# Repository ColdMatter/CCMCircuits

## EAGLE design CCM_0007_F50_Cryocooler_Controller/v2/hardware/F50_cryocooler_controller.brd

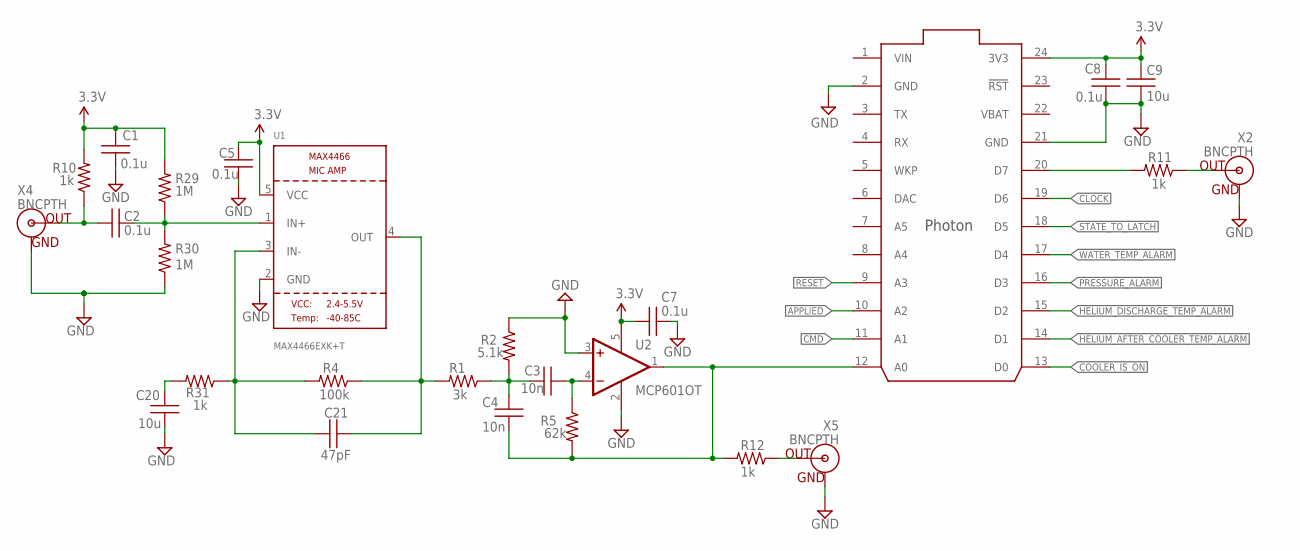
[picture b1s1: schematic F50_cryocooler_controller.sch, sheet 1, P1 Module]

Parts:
C1, C2, C5, C7, C8: 0.1u; 0603
C3, C4: 10n; 0603
C9: 10u; 0805
C20: 10u; 0603
C21: 47pF; 0603
R1: 3k; 0603
R2: 5.1k; 0603
R4: 100k; 0603
R5: 62k; 0603
R10, R11, R12, R31: 1k; 0603
R29, R30: 1M; 0603
U1: MAX4466EXK+T; SC70-5
U2: MCP601OT; SOT23-5
U3: PHOTON_WITH_HEADERS; PHOTON
X2, X4, X5: BNCPTH; BNC

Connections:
3.3V: C1.1, C5.1, C7.1, C8.1, C9.2, R10.2, R29.2, U1.5 (VCC), U2.5 (V+), U3.24 (3V3)
APPLIED: U3.10 (A2); also elsewhere on the board
AUDIO_IN: C21.2, R1.2, R4.1, U1.4 (OUT)
CLOCK: U3.19 (D6); also elsewhere on the board
CMD: U3.11 (A1); also elsewhere on the board
COOLER_IS_ON: U3.13 (D0); also elsewhere on the board
GND: C1.2, C5.2, C7.2, C8.2, C9.1, C20.2, R2.1, R30.1, U1.2 (GND), U2.2 (V-), U2.3 (+IN), U3.2 (GND), U3.21 (GND), X2.GND, X4.GND, X5.GND; also elsewhere on the board
HELIUM_AFTER_COOLER_TEMP_ALARM: U3.14 (D1); also elsewhere on the board
HELIUM_DISCHARGE_TEMP_ALARM: U3.15 (D2); also elsewhere on the board
unnamed: C2.1, R10.1, X4.S (OUT)
unnamed: C2.2, R29.1, R30.2, U1.1 (IN+)
unnamed: C21.1, R4.2, R31.1, U1.3 (IN-)
unnamed: C20.1, R31.2
unnamed: C3.1, C4.2, R1.1, R2.2
unnamed: C3.2, R5.1, U2.4 (-IN)
unnamed: R11.2, U3.20 (D7)
unnamed: C4.1, R5.2, R12.2, U2.1 (OUT), U3.12 (A0)
PRESSURE_ALARM: U3.16 (D3); also elsewhere on the board
RESET: U3.9 (A3); also elsewhere on the board
STATE_TO_LATCH: U3.18 (D5); also elsewhere on the board
SYNC_OUT: R11.1, X2.S (OUT)
TRIGGER_OUT: R12.1, X5.S (OUT)
VBAT: U3.22 (VBAT)
VIN: U3.1 (VIN)
WATER_TEMP_ALARM: U3.17 (D4); also elsewhere on the board

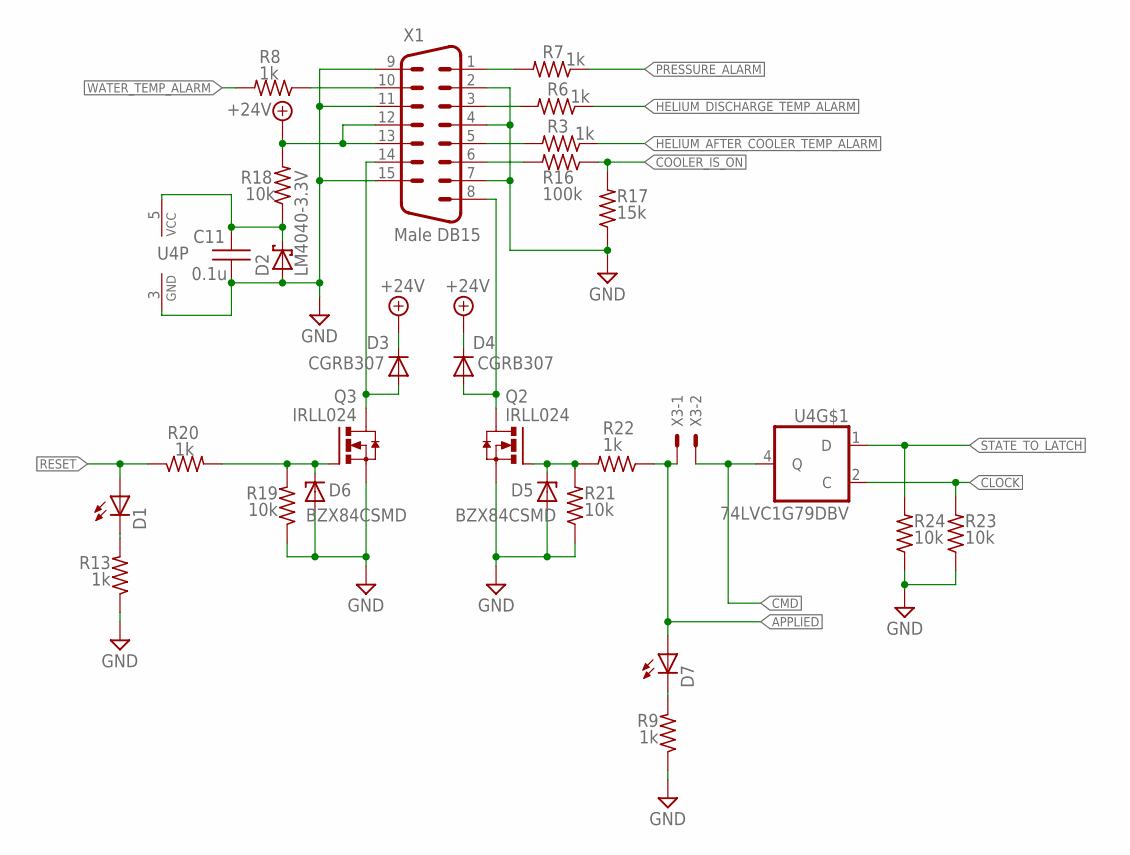
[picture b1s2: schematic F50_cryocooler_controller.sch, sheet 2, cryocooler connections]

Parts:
C11: 0.1u; 0603
D1, D7: LED0603
D2: LM4040-3.3V; SOT23
D3, D4: CGRB307; DO214AA
D5, D6: BZX84CSMD; TO236
Q2, Q3: IRLL024; SOT223
R3, R6, R7, R8, R9, R13, R20, R22: 1k; 0603
R16: 100k; 0603
R17: 15k; 0603
R18, R19, R21, R23, R24: 10k; 0603
U4: 74LVC1G79DBV; SOT23-5
X1: Male DB15; M15HP
X3: 22-23-2021

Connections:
+24V: D3.C, D4.C, R18.2, X1.12, X1.13
APPLIED: D7.A, R22.1, X3.1; also elsewhere on the board
CLOCK: R23.2, U4.2 (C); also elsewhere on the board
CMD: U4.4 (Q), X3.2; also elsewhere on the board
COOLER_IS_ON: R16.1, R17.2; also elsewhere on the board
GND: C11.2, D2.2 (A), D5.A, D6.A, Q2.3 (S), Q3.3 (S), R9.1, R13.1, R17.1, R19.1, R21.1, R23.1, R24.1, U4.3 (GND), X1.2, X1.4, X1.7, X1.9, X1.11, X1.15; also elsewhere on the board
HELIUM_AFTER_COOLER_TEMP_ALARM: R3.1; also elsewhere on the board
HELIUM_DISCHARGE_TEMP_ALARM: R6.1; also elsewhere on the board
unnamed: R8.1, X1.10
unnamed: R16.2, X1.6
unnamed: R7.2, X1.1
unnamed: D4.A, Q2.4 (D), X1.8
unnamed: R6.2, X1.3
unnamed: D5.C, Q2.1 (G), R21.2, R22.2
unnamed: C11.1, D2.1 (C), R18.1, U4.5 (VCC)
unnamed: R3.2, X1.5
unnamed: D1.C, R13.2
unnamed: D7.C, R9.2
unnamed: D3.A, Q3.4 (D), X1.14
unnamed: D6.C, Q3.1 (G), R19.2, R20.2
PRESSURE_ALARM: R7.1; also elsewhere on the board
RESET: D1.A, R20.1; also elsewhere on the board
STATE_TO_LATCH: R24.2, U4.1 (D); also elsewhere on the board
WATER_TEMP_ALARM: R8.2; also elsewhere on the board

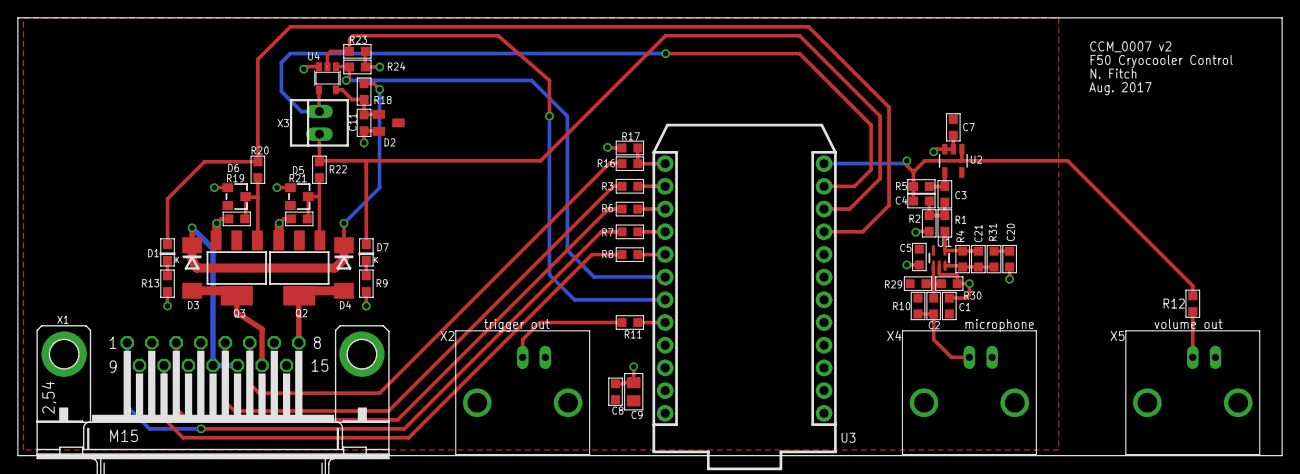
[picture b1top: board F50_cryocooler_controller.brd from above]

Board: 2 copper layers, 141.5 x 49.0 mm, 54 parts (0 on the bottom side), 36 nets.

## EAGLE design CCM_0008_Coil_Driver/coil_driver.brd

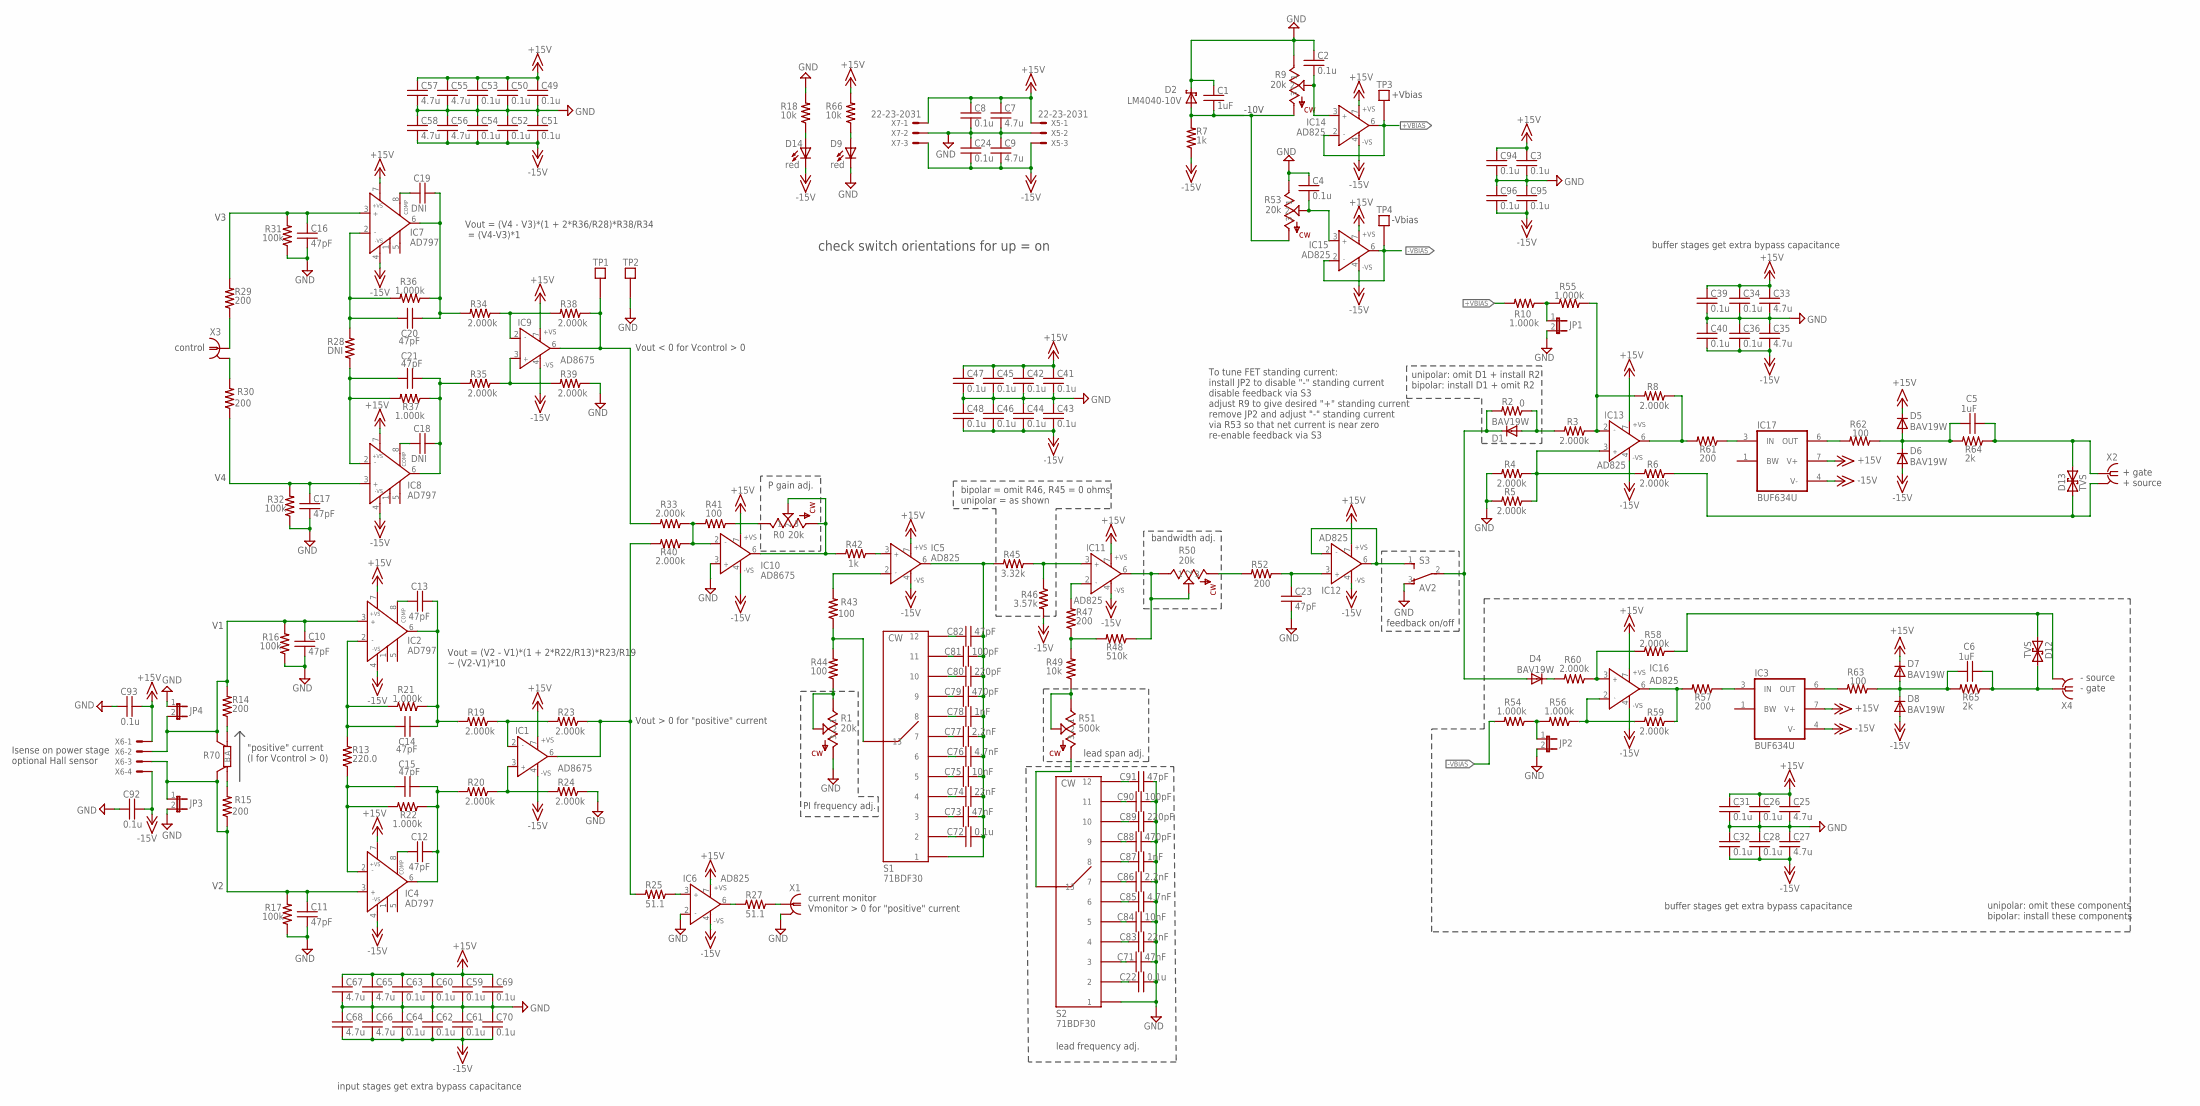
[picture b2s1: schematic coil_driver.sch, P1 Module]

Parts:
C1, C5, C6: 1uF; 0603
C2, C3, C4, C8, C22, C24, C26, C28, C31, C32, C34, C36, C39, C40, C41, C42, C43, C44, C45, C46, C47, C48, C49, C50, C51, C52, C53, C54, C59, C60, C61, C62, C63, C64, C69, C70, C72, C92, C93, C94, C95, C96: 0.1u; 0603
C7, C9, C25, C27, C33, C35, C55, C56, C57, C58, C65, C66, C67, C68: 4.7u; 0603
C10, C11, C12, C13, C14, C15, C16, C17, C20, C21, C23, C82, C91: 47pF; 0603
C18, C19: DNI; 0603
C71, C73: 47nF; 0603
C74, C83: 22nF; 0603
C75, C84: 10nF; 0603
C76, C85: 4.7nF; 0603
C77, C86: 2.2nF; 0603
C78, C87: 1nF; 0603
C79, C88: 470pF; 0603
C80, C89: 220pF; 0603
C81, C90: 100pF; 0603
D1, D4, D5, D6, D7, D8: BAV19W; SOD123
D2: LM4040-10V; SOT23
D9, D14: red; LED0603
D12, D13: TVS; SMA-DIODE
IC1, IC9, IC10: AD8675; SO8
IC2, IC4, IC7, IC8: AD797; SO8
IC3, IC17: BUF634U; SO08
IC5, IC6, IC11, IC14, IC15, IC16: AD825; SO08
IC12, IC13: AD825; SO8
JP1, JP2, JP3, JP4: JP1E; JP1
R0: 20k; 3590
R1, R9, R50, R53: 20k; SP19L
R2: 0; 0603
R3, R4, R5, R6, R8, R19, R20, R23, R24, R33, R34, R35, R38, R39, R40, R58, R59, R60: 2.000k; 0603
R7, R42: 1k; 0603
R10, R21, R22, R36, R37, R54, R55, R56: 1.000k; 0603
R13: 220.0; 0603
R14, R15, R29, R30, R47, R52, R57, R61: 200; 0603
R16, R17, R31, R32: 100k; 0603
R18, R49, R66: 10k; 0603
R25, R27: 51.1; 0603
R28: DNI; 0603
R41, R43, R44, R62, R63: 100; 0603
R45: 3.32k; 0603
R46: 3.57k; 0603
R48: 510k; 0603
R51: 500k; SP19L
R64, R65: 2k; 0603
R70: RSENSE; 22-23-2041
S1, S2: 71BDF30; 71BDF
S3: AV2; SPDT-AV2
TP1, TP2, TP3, TP4: TESTPOINT
X1, X3: 1-227161-0; AMP_227161
X2, X4: BU-SMA-H
X5, X7: 22-23-2031
X6: 22-23-2041

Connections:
+15V: C3.1, C7.1, C8.1, C25.1, C26.1, C31.1, C33.1, C34.1, C39.1, C41.1, C42.1, C45.1, C47.1, C49.1, C50.1, C53.1, C55.1, C57.1, C59.1, C60.1, C63.1, C65.1, C67.1, C69.1, C93.2, C94.1, D5.C, D7.C, IC1.7 (+VS), IC2.7 (+VS), IC3.7 (V+), IC4.7 (+VS), IC5.7 (+VS), IC6.7 (+VS), IC7.7 (+VS), IC8.7 (+VS), IC9.7 (+VS), IC10.7 (+VS), IC11.7 (+VS), IC12.7 (+VS), IC13.7 (+VS), IC14.7 (+VS), IC15.7 (+VS), IC16.7 (+VS), IC17.7 (V+), R66.2, X5.1, X6.1, X7.1
+GATE: C5.2, D13.C (2), R64.1, X2.1
+SOURCE: D13.A (1), R6.1, X2.2, X2.3 (2), X2.4 (2), X2.5 (2)
+VBIAS: IC14.2 (IN-), IC14.6 (OUT), R10.2, TP3.P$1
-10V: C1.2, D2.2 (A), R7.2, R9.E (3), R53.E (3)
-15V: C9.2, C24.2, C27.2, C28.2, C32.2, C35.2, C36.2, C40.2, C43.2, C44.2, C46.2, C48.2, C51.2, C52.2, C54.2, C56.2, C58.2, C61.2, C62.2, C64.2, C66.2, C68.2, C70.2, C92.2, C95.2, C96.2, D6.A, D8.A, D14.C, IC1.4 (-VS), IC2.4 (-VS), IC3.4 (V-), IC4.4 (-VS), IC5.4 (-VS), IC6.4 (-VS), IC7.4 (-VS), IC8.4 (-VS), IC9.4 (-VS), IC10.4 (-VS), IC11.4 (-VS), IC12.4 (-VS), IC13.4 (-VS), IC14.4 (-VS), IC15.4 (-VS), IC16.4 (-VS), IC17.4 (V-), R7.1, R46.2, X5.3, X6.4, X7.3
-GATE: C6.2, D12.C (2), R65.1, X4.1
-SOURCE: D12.A (1), R58.1, X4.2, X4.3 (2), X4.4 (2), X4.5 (2)
-VBIAS: IC15.2 (IN-), IC15.6 (OUT), R54.2, TP4.P$1
unnamed: R1.A (1), R1.S (2), R44.1
unnamed: D1.A, R2.1, R3.2
unnamed: JP1.1, R10.1, R55.2
unnamed: D4.C, R60.2
unnamed: IC13.3 (IN+), R4.1, R5.1, R6.2
unnamed: C14.1, IC2.2 (IN-), R13.2, R21.2
unnamed: R14.1, R70.1 (A)
unnamed: IC13.2 (IN-), R3.1, R8.2, R55.1
unnamed: C2.2, IC14.3 (IN+), R9.S (2)
unnamed: R15.2, R70.4 (B)
unnamed: C15.1, IC4.2 (IN-), R13.1, R22.2
unnamed: C12.1, IC4.8 (COMP)
unnamed: C12.2, C15.2, IC4.6 (OUT), R20.2, R22.1
unnamed: C13.1, IC2.8 (COMP)
unnamed: C13.2, C14.2, IC2.6 (OUT), R19.2, R21.1
unnamed: IC1.2 (IN-), R19.1, R23.2
unnamed: IC1.3 (IN+), R20.1, R24.2
unnamed: IC1.6 (OUT), R23.1, R25.2, R40.2
unnamed: IC6.3 (IN+), R25.1
unnamed: R27.1, X1.1
unnamed: C20.1, IC7.2 (IN-), R28.2, R36.2
unnamed: C16.1, IC7.3 (IN+), R29.2, R31.2
unnamed: C17.1, IC8.3 (IN+), R30.1, R32.2
unnamed: R29.1, X3.1
unnamed: R30.2, X3.2
unnamed: C21.1, IC8.2 (IN-), R28.1, R37.2
unnamed: C18.1, IC8.8 (COMP)
unnamed: C18.2, C21.2, IC8.6 (OUT), R35.2, R37.1
unnamed: C19.1, IC7.8 (COMP)
unnamed: C19.2, C20.2, IC7.6 (OUT), R34.2, R36.1
unnamed: IC9.2 (IN-), R34.1, R38.2
unnamed: IC9.3 (IN+), R35.1, R39.2
unnamed: IC9.6 (OUT), R33.2, R38.1, TP1.P$1
unnamed: IC10.2 (IN-), R33.1, R40.1, R41.2
unnamed: IC11.3 (IN+), R45.1, R46.1
unnamed: IC10.6 (OUT), R0.2, R0.3, R42.2
unnamed: IC5.3 (IN+), R42.1
unnamed: IC5.2 (IN-), R43.2
unnamed: R43.1, R44.2, S1.13
unnamed: R51.E (3), S2.13
unnamed: IC11.2 (IN-), R47.2
unnamed: R47.1, R48.2, R49.2
unnamed: IC11.6 (OUT), R48.1, R50.A (1), R50.S (2)
unnamed: R49.1, R51.A (1), R51.S (2)
unnamed: R50.E (3), R52.2
unnamed: C23.1, IC12.3 (IN+), R52.1
unnamed: IC12.2 (IN-), IC12.6 (OUT), S3.1
unnamed: D1.C, D4.A, R2.2, S3.2
unnamed: C4.2, IC15.3 (IN+), R53.S (2)
unnamed: JP2.1, R54.1, R56.2
unnamed: IC16.2 (IN-), R56.1, R59.2
unnamed: IC16.3 (IN+), R58.2, R60.1
unnamed: IC16.6 (OUT), R57.2, R59.1
unnamed: D9.A, R66.1
unnamed: IC3.3 (IN), R57.1
unnamed: IC17.3 (IN), R61.1
unnamed: IC13.6 (OUT), R8.1, R61.2
unnamed: IC17.6 (OUT), R62.2
unnamed: IC3.6 (OUT), R63.2
unnamed: C5.1, D5.A, D6.C, R62.1, R64.2
unnamed: C6.1, D7.A, D8.C, R63.1, R65.2
unnamed: D14.A, R18.1
unnamed: C72.2, C73.2, C74.2, C75.2, C76.2, C77.2, C78.2, C79.2, C80.2, C81.2, C82.2, IC5.6 (OUT), R45.2, S1.1
unnamed: C72.1, S1.2
unnamed: C73.1, S1.3
unnamed: C74.1, S1.4
unnamed: R0.1, R41.1
unnamed: C75.1, S1.5
unnamed: C76.1, S1.6
unnamed: C77.1, S1.7
unnamed: C78.1, S1.8
unnamed: C79.1, S1.9
unnamed: C80.1, S1.10
unnamed: C81.1, S1.11
unnamed: C82.1, S1.12
unnamed: C22.1, S2.2
unnamed: C71.1, S2.3
unnamed: C83.1, S2.4
unnamed: C84.1, S2.5
unnamed: C85.1, S2.6
unnamed: C86.1, S2.7
unnamed: C87.1, S2.8
unnamed: C88.1, S2.9
unnamed: C89.1, S2.10
unnamed: C90.1, S2.11
unnamed: C91.1, S2.12
V+: C11.1, IC4.3 (IN+), JP3.1, R15.1, R17.2, R70.3 (SB), X6.3
V-: C10.1, IC2.3 (IN+), JP4.2, R14.2, R16.2, R70.2 (SA), X6.2

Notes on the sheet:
check switch orientations for up = on
"positive" current (I for Vcontrol > 0)
control
bipolar = omit R46, R45 = 0 ohms unipolar = as shown
feedback on/off
PI frequency adj.
unipolar: omit D1 + install R2 bipolar: install D1 + omit R2
To tune FET standing current: install JP2 to disable "-" standing current disable feedback via S3 adjust R9 to give desired "+" standing current remove JP2 and adjust "-" standing current via R53 so that net current is near zero re-enable feedback via S3
+ gate + source
- source - gate
unipolar: omit these components bipolar: install these components
lead span adj.
P gain adj.
input stages get extra bypass capacitance
Isense on power stage optional Hall sensor
bandwidth adj.
buffer stages get extra bypass capacitance
lead frequency adj.
-10V
Vout = (V2 - V1)*(1 + 2*R22/R13)*R23/R19 ~ (V2-V1)*10
Vout > 0 for "positive" current
current monitor Vmonitor > 0 for "positive" current
Vout = (V4 - V3)*(1 + 2*R36/R28)*R38/R34 = (V4-V3)*1
Vout < 0 for Vcontrol > 0
+Vbias
-Vbias

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
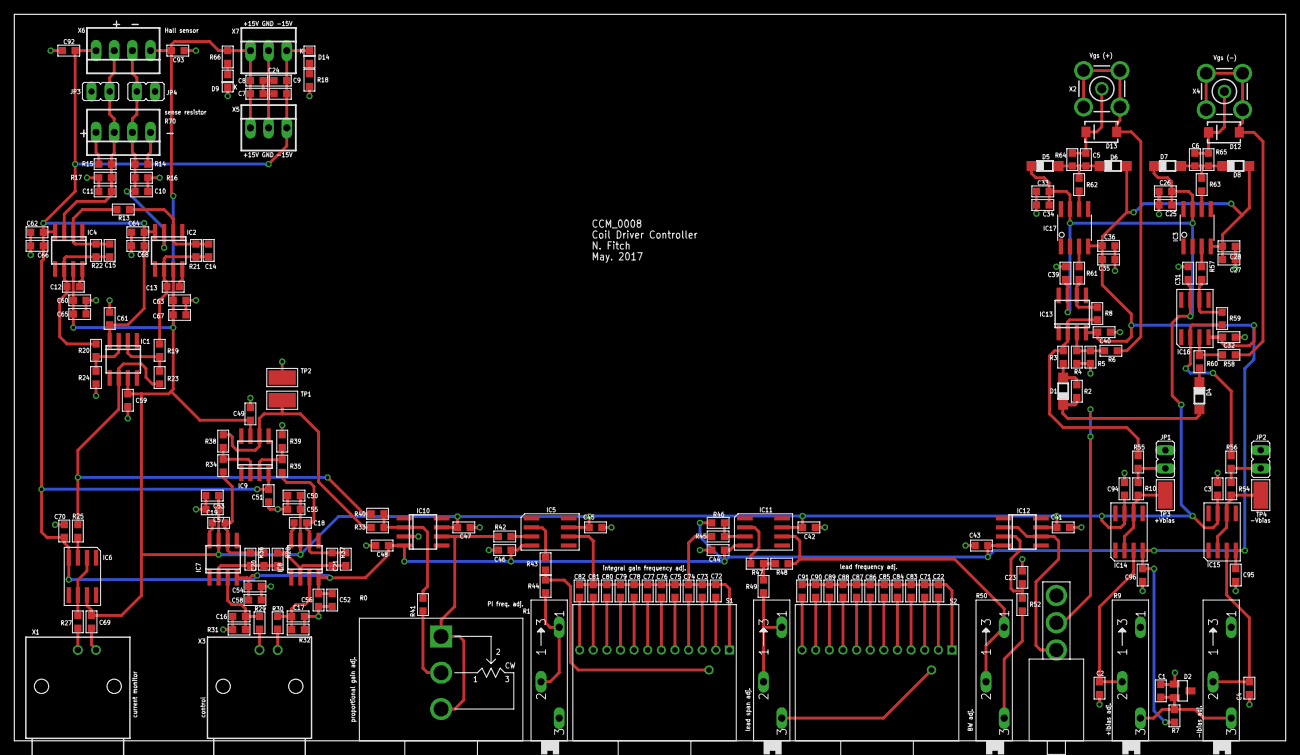
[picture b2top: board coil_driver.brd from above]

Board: 2 copper layers, 177.8 x 101.6 mm, 203 parts (0 on the bottom side), 99 nets.

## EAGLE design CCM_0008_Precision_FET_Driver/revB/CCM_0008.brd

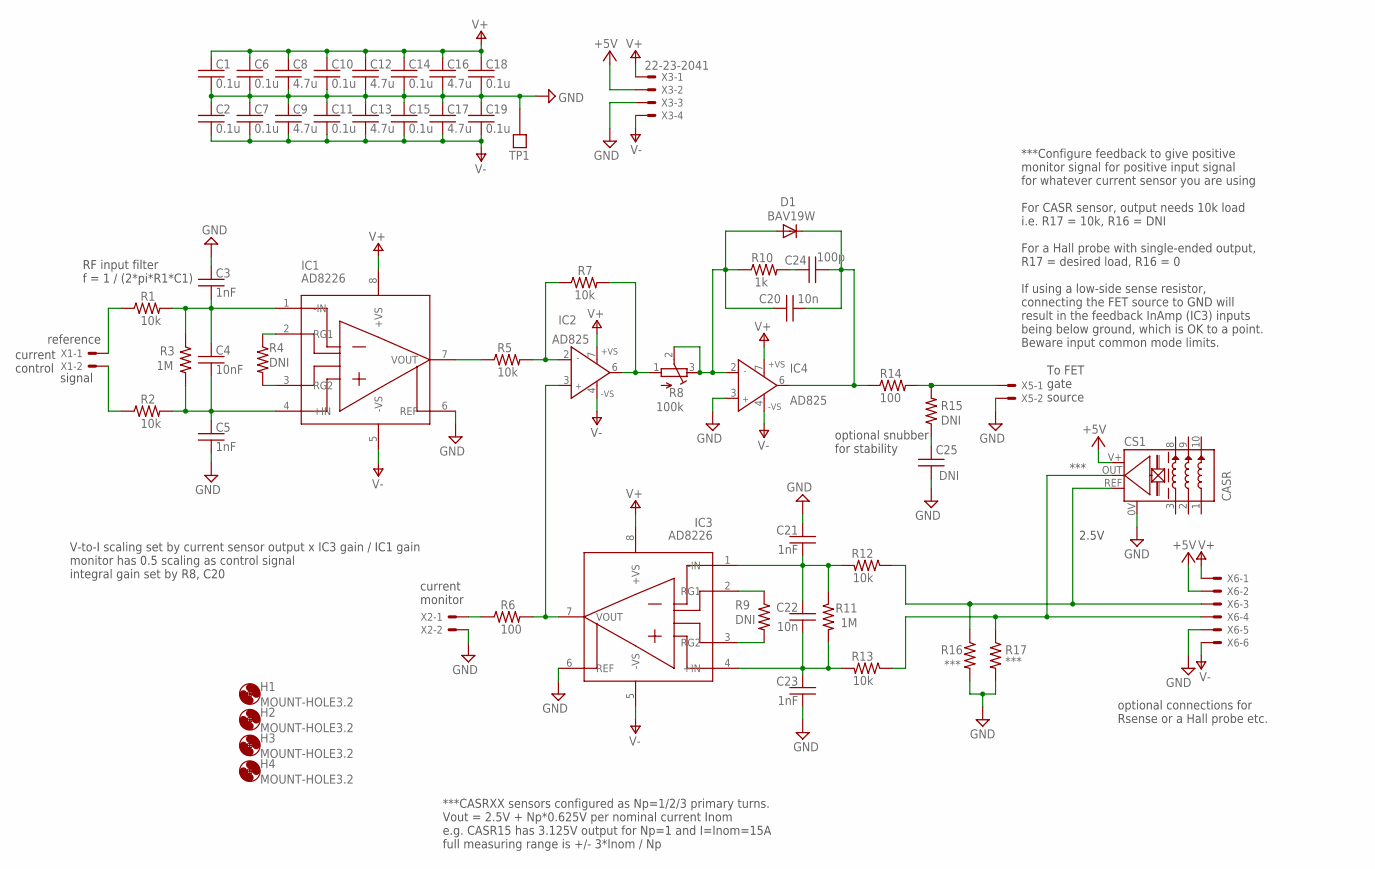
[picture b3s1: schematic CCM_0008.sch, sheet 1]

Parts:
C1, C2, C6, C7, C10, C11, C14, C15, C18, C19: 0.1u; 0603
C3, C5, C21, C23: 1nF; 0603
C4: 10nF; 0603
C8, C9, C12, C13, C16, C17: 4.7u; 0603
C20, C22: 10n; 0603
C24: 100p; 0603
C25: DNI; 0603
CS1: CASR
D1: BAV19W; SOD123
H1, H2, H3, H4: MOUNT-HOLE3.2; 3,2
IC1, IC3: AD8226; SO08
IC2, IC4: AD825; SO8
R1, R2, R5, R7, R12, R13: 10k; 0603
R3, R11: 1M; 0603
R4, R9, R15: DNI; 0603
R6, R14: 100; 0603
R8: 100k; RTRIM3296W
R10: 1k; 0603
R16, R17: ***; 0603
TP1: TESTPOINT
X1, X2, X5: 22-23-2021
X3: 22-23-2041
X6: 22-23-2061

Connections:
+5V: CS1.V+, X3.2, X6.2
GND: C1.2, C2.1, C3.1, C5.2, C6.2, C7.1, C8.2, C9.1, C10.2, C11.1, C12.2, C13.1, C14.2, C15.1, C16.2, C17.1, C18.2, C19.1, C21.1, C23.2, C25.2, CS1.0V, IC1.6 (REF), IC3.6 (REF), IC4.3 (IN+), R16.2, R17.2, TP1.P$1, X2.2, X3.3, X5.2, X6.5
unnamed: R2.1, X1.2
unnamed: R1.1, X1.1
unnamed: C20.1, C24.1, D1.C, IC4.6 (OUT), R14.1
unnamed: IC1.2 (RG1), R4.1
unnamed: C3.2, C4.1, IC1.1 (-IN), R1.2, R3.1
unnamed: C4.2, C5.1, IC1.4 (+IN), R2.2, R3.2
unnamed: R6.1, X2.1
unnamed: IC1.3 (RG2), R4.2
unnamed: IC2.3 (IN+), IC3.7 (VOUT), R6.2
unnamed: IC1.7 (VOUT), R5.1
unnamed: IC2.2 (IN-), R5.2, R7.1
unnamed: IC2.6 (OUT), R7.2, R8.1 (A)
unnamed: CS1.OUT (VOUT), R13.1, R17.1, X6.4
unnamed: IC3.2 (RG1), R9.1
unnamed: IC3.3 (RG2), R9.2
unnamed: C21.2, C22.1, IC3.1 (-IN), R11.1, R12.2
unnamed: C22.2, C23.1, IC3.4 (+IN), R11.2, R13.2
unnamed: CS1.REF (VREF), R12.1, R16.1, X6.3
unnamed: C25.1, R15.1
unnamed: C24.2, R10.2
unnamed: C20.2, D1.A, IC4.2 (IN-), R8.2 (S), R8.3 (E), R10.1
unnamed: R14.2, R15.2, X5.1
V+: C1.1, C6.1, C8.1, C10.1, C12.1, C14.1, C16.1, C18.1, IC1.8 (+VS), IC2.7 (+VS), IC3.8 (+VS), IC4.7 (+VS), X3.1, X6.1
V-: C2.2, C7.2, C9.2, C11.2, C13.2, C15.2, C17.2, C19.2, IC1.5 (-VS), IC2.4 (-VS), IC3.5 (-VS), IC4.4 (-VS), X3.4, X6.6

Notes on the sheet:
current control
RF input filter f = 1 / (2*pi*R1*C1)
optional snubber for stability
current monitor
***Configure feedback to give positive monitor signal for positive input signal for whatever current sensor you are using For CASR sensor, output needs 10k load i.e. R17 = 10k, R16 = DNI For a Hall probe with single-ended output, R17 = desired load, R16 = 0 If using a low-side sense resistor, conne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
signal
reference
To FET gate source
optional connections for Rsense or a Hall probe etc.
V-to-I scaling set by current sensor output x IC3 gain / IC1 gain monitor has 0.5 scaling as control signal integral gain set by R8, C20
***CASRXX sensors configured as Np=1/2/3 primary turns. Vout = 2.5V + Np*0.625V per nominal current Inom e.g. CASR15 has 3.125V output for Np=1 and I=Inom=15A full measuring range is +/- 3*Inom / Np
***
2.5V

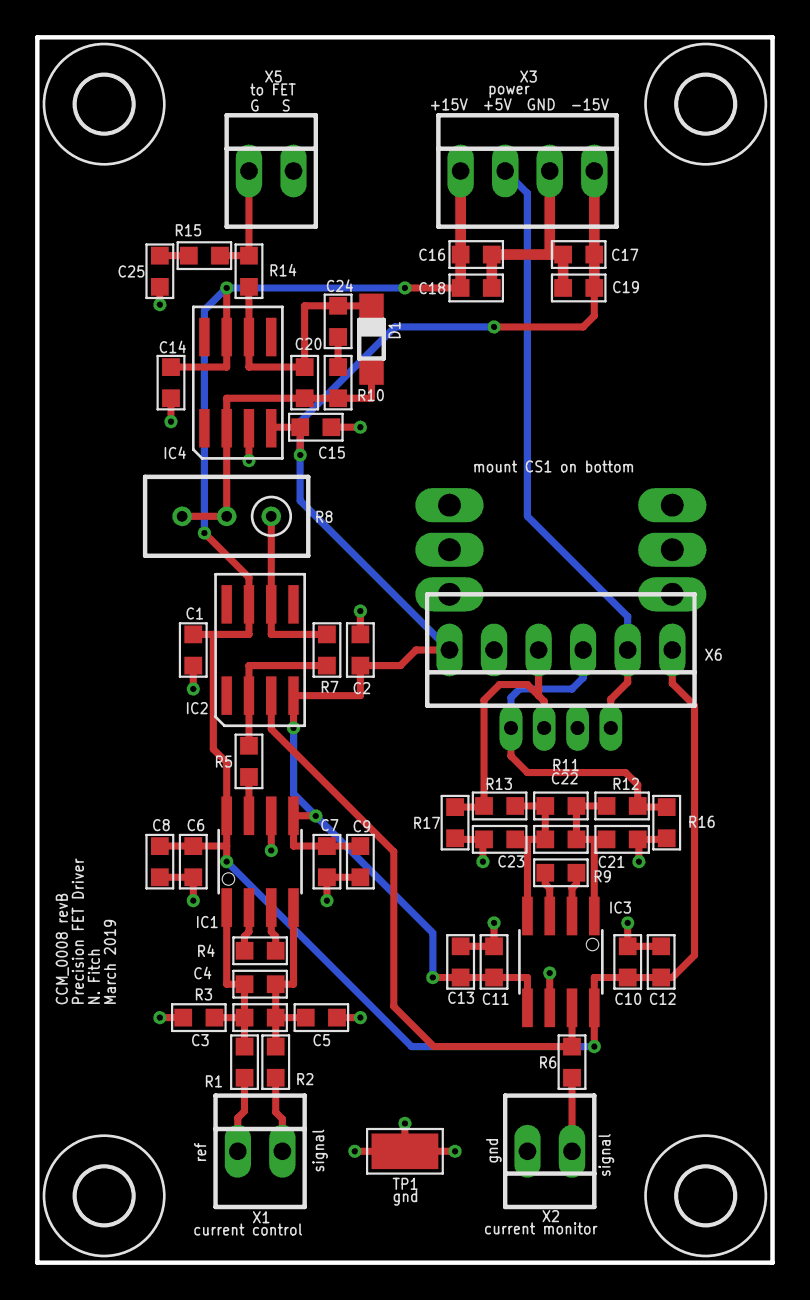
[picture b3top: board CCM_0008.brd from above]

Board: 2 copper layers, 41.9 x 69.8 mm, 58 parts (1 on the bottom side), 26 nets.

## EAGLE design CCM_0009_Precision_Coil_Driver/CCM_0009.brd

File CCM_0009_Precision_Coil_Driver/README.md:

Precision Coil Driver
===========
     
This is a low-noise, low-current, bipolar precision current supply.

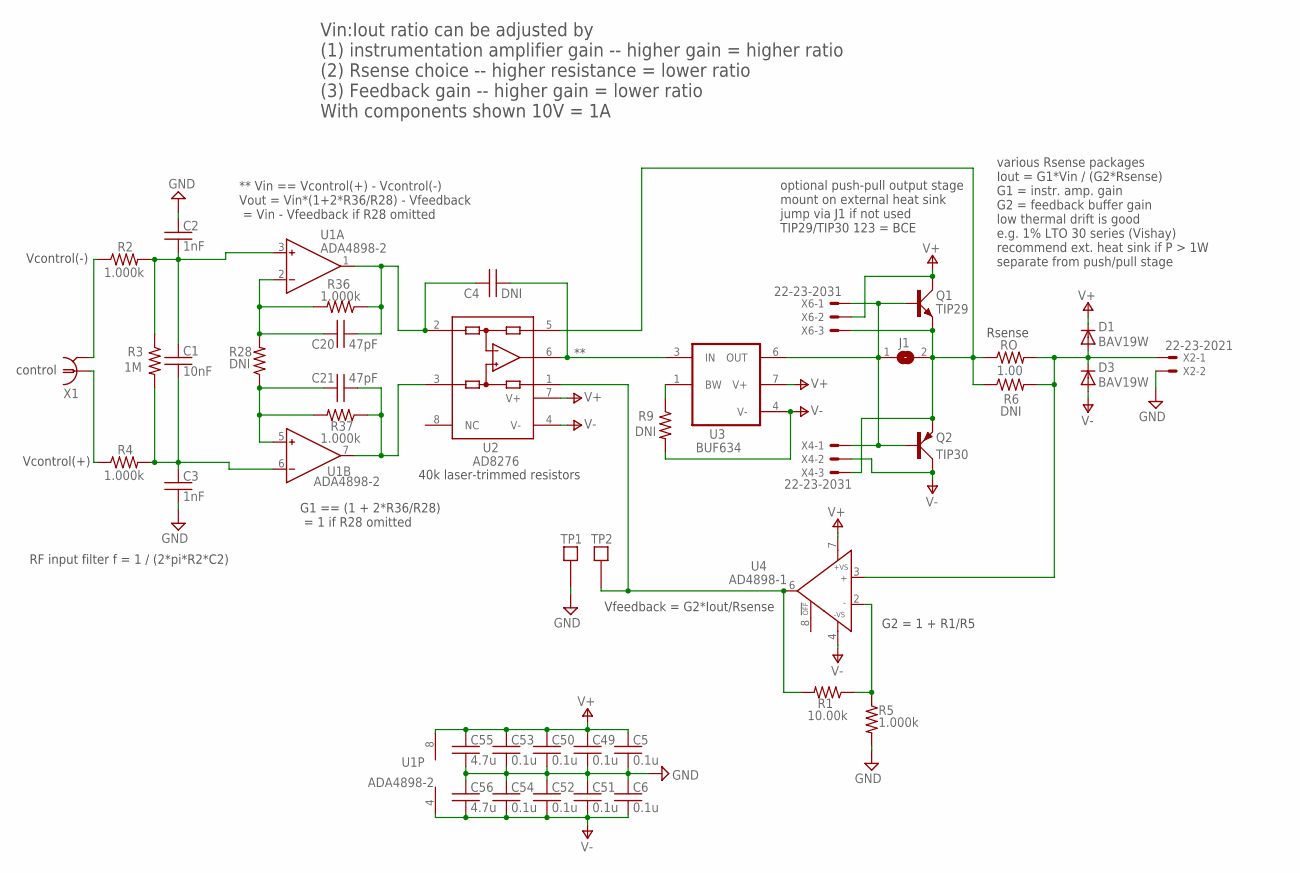
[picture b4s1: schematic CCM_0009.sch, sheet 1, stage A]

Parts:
C1: 10nF; 0603
C2, C3: 1nF; 0603
C4: DNI; 0603
C5, C6, C49, C50, C51, C52, C53, C54: 0.1u; 0603
C20, C21: 47pF; 0603
C55, C56: 4.7u; 0603
D1, D3: BAV19W; SOD123
J1: SJ
Q1: TIP29; TO220AV
Q2: TIP30; TO220AV
R1: 10.00k; 0603
R2, R4, R5, R36, R37: 1.000k; 0603
R3: 1M; 0603
R6: DNI; 2512
R9, R28: DNI; 0603
RO: 1.00; LTO30
TP1, TP2: TESTPOINT
U1: ADA4898-2; SO8
U2: AD8276; SO8
U3: BUF634; SO8
U4: AD4898-1; SO8
X1: 1-227161-0; AMP_227161
X2: 22-23-2021
X4, X6: 22-23-2031

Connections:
GND: C2.1, C3.2, C5.2, C6.1, C49.2, C50.2, C51.1, C52.1, C53.2, C54.1, C55.2, C56.1, R5.2, TP1.P$1, X2.2; also elsewhere on the board
unnamed: R2.1, X1.2
unnamed: R4.1, X1.1
unnamed: C4.2, U2.6 (OUT), U3.3 (IN)
unnamed: C1.1, C2.2, R2.2, R3.1, U1.3 (IN+)
unnamed: C1.2, C3.1, R3.2, R4.2, U1.6 (IN-)
unnamed: R1.1, R5.1, U4.2 (IN-)
unnamed: J1.1, Q1.B, Q2.B, U3.6 (OUT), X4.1, X6.1
unnamed: D1.A, D3.C, R6.2, RO.P$2 (2), U4.3 (IN+), X2.1
unnamed: J1.2, Q1.E, Q2.E, R6.1, RO.P$1 (1), U2.5 (SENSE), X4.3, X6.3
unnamed: R9.1, U3.1 (BW)
unnamed: R1.2, TP2.P$1, U2.1 (REF), U4.6 (OUT)
unnamed: C20.1, R28.2, R36.2, U1.2 (IN-)
unnamed: C21.1, R28.1, R37.2, U1.5 (IN+)
unnamed: C21.2, R37.1, U1.7 (OUT), U2.3 (+IN)
unnamed: C4.1, C20.2, R36.1, U1.1 (OUT), U2.2 (-IN)
V+: C5.1, C49.1, C50.1, C53.1, C55.1, D1.C, Q1.C, U1.8 (V+), U2.7 (V+), U3.7 (V+), U4.7 (+VS), X6.2; also elsewhere on the board
V-: C6.2, C51.2, C52.2, C54.2, C56.2, D3.A, Q2.C, R9.2, U1.4 (V-), U2.4 (V-), U3.4 (V-), U4.4 (-VS), X4.2; also elsewhere on the board

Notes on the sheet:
control
RF input filter f = 1 / (2*pi*R2*C2)
optional push-pull output stage mount on external heat sink jump via J1 if not used TIP29/TIP30 123 = BCE
40k laser-trimmed resistors
Vcontrol(+)
Vcontrol(-)
various Rsense packages Iout = G1*Vin / (G2*Rsense) G1 = instr. amp. gain G2 = feedback buffer gain low thermal drift is good e.g. 1% LTO 30 series (Vishay) recommend ext. heat sink if P > 1W separate from push/pull stage
** Vin == Vcontrol(+) - Vcontrol(-) Vout = Vin*(1+2*R36/R28) - Vfeedback = Vin - Vfeedback if R28 omitted
G1 == (1 + 2*R36/R28) = 1 if R28 omitted
Vfeedback = G2*Iout/Rsense
Rsense
G2 = 1 + R1/R5
Vin:Iout ratio can be adjusted by (1) instrumentation amplifier gain -- higher gain = higher ratio (2) Rsense choice -- higher resistance = lower ratio (3) Feedback gain -- higher gain = lower ratio With components shown 10V = 1A

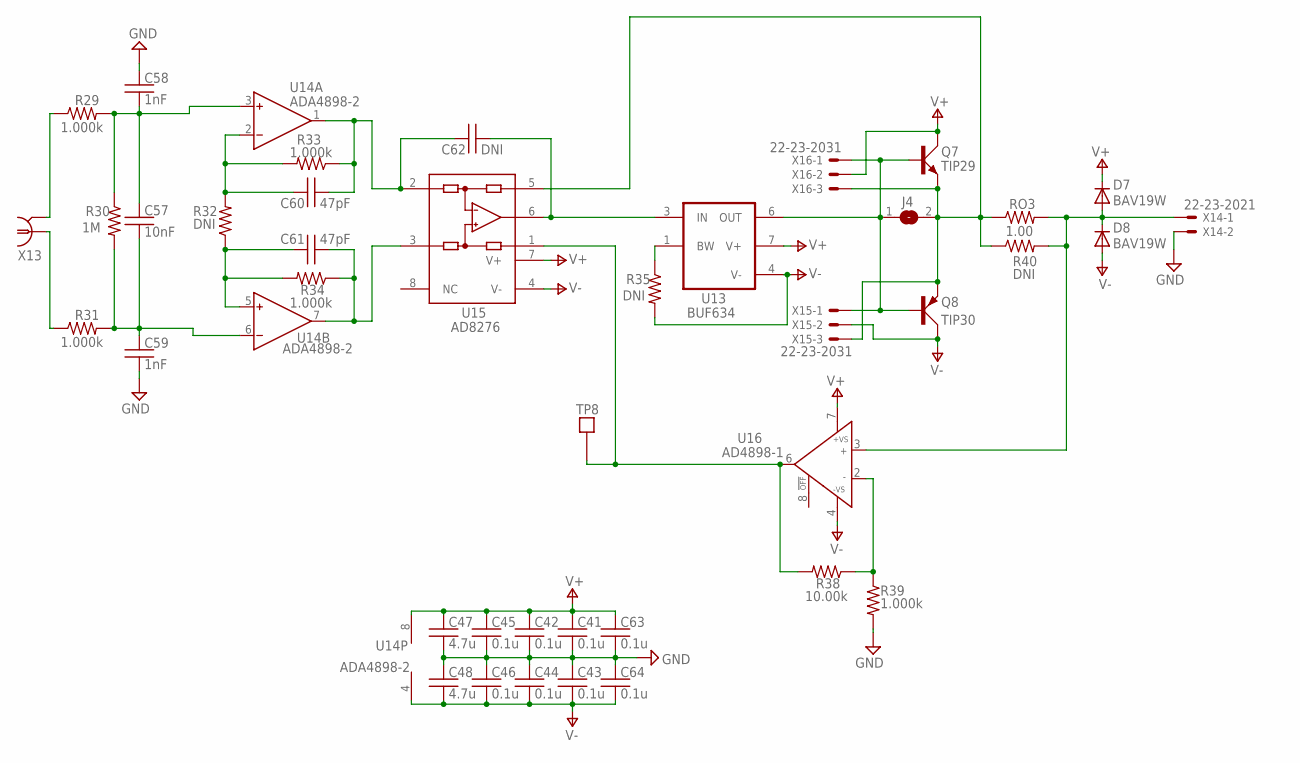
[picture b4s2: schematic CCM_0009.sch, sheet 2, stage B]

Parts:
C41, C42, C43, C44, C45, C46, C63, C64: 0.1u; 0603
C47, C48: 4.7u; 0603
C57: 10nF; 0603
C58, C59: 1nF; 0603
C60, C61: 47pF; 0603
C62: DNI; 0603
D7, D8: BAV19W; SOD123
J4: SJ
Q7: TIP29; TO220AV
Q8: TIP30; TO220AV
R29, R31, R33, R34, R39: 1.000k; 0603
R30: 1M; 0603
R32, R35: DNI; 0603
R38: 10.00k; 0603
R40: DNI; 2512
RO3: 1.00; LTO30
TP8: TESTPOINT
U13: BUF634; SO8
U14: ADA4898-2; SO8
U15: AD8276; SO8
U16: AD4898-1; SO8
X13: 1-227161-0; AMP_227161
X14: 22-23-2021
X15, X16: 22-23-2031

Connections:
GND: C41.2, C42.2, C43.1, C44.1, C45.2, C46.1, C47.2, C48.1, C58.1, C59.2, C63.2, C64.1, R39.2, X14.2; also elsewhere on the board
unnamed: C57.1, C58.2, R29.2, R30.1, U14.3 (IN+)
unnamed: C57.2, C59.1, R30.2, R31.2, U14.6 (IN-)
unnamed: R29.1, X13.2
unnamed: R31.1, X13.1
unnamed: C60.1, R32.2, R33.2, U14.2 (IN-)
unnamed: C61.1, R32.1, R34.2, U14.5 (IN+)
unnamed: C61.2, R34.1, U14.7 (OUT), U15.3 (+IN)
unnamed: C60.2, C62.1, R33.1, U14.1 (OUT), U15.2 (-IN)
unnamed: J4.1, Q7.B, Q8.B, U13.6 (OUT), X15.1, X16.1
unnamed: D7.A, D8.C, R40.2, RO3.P$2 (2), U16.3 (IN+), X14.1
unnamed: R35.1, U13.1 (BW)
unnamed: C62.2, U13.3 (IN), U15.6 (OUT)
unnamed: R38.2, TP8.P$1, U15.1 (REF), U16.6 (OUT)
unnamed: J4.2, Q7.E, Q8.E, R40.1, RO3.P$1 (1), U15.5 (SENSE), X15.3, X16.3
unnamed: R38.1, R39.1, U16.2 (IN-)
V+: C41.1, C42.1, C45.1, C47.1, C63.1, D7.C, Q7.C, U13.7 (V+), U14.8 (V+), U15.7 (V+), U16.7 (+VS), X16.2; also elsewhere on the board
V-: C43.2, C44.2, C46.2, C48.2, C64.2, D8.A, Q8.C, R35.2, U13.4 (V-), U14.4 (V-), U15.4 (V-), U16.4 (-VS), X15.2; also elsewhere on the board

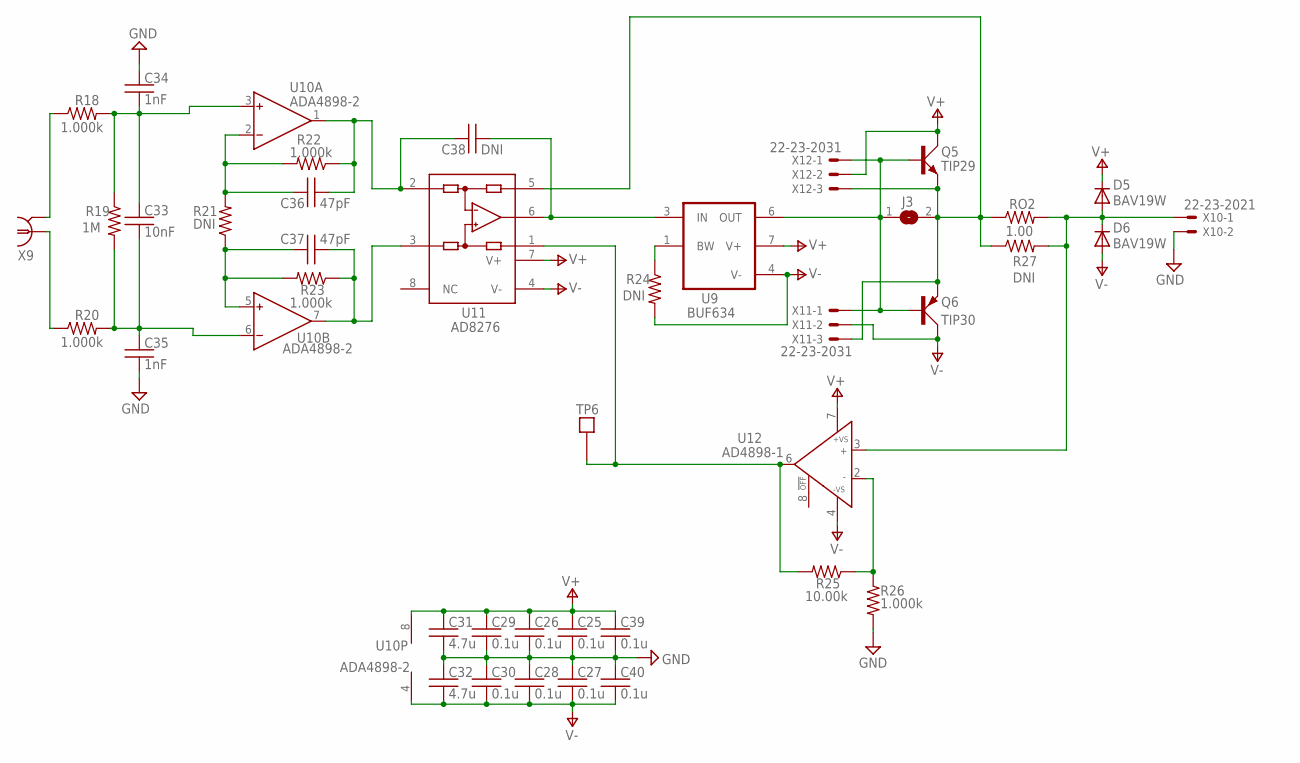
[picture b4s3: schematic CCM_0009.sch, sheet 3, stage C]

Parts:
C25, C26, C27, C28, C29, C30, C39, C40: 0.1u; 0603
C31, C32: 4.7u; 0603
C33: 10nF; 0603
C34, C35: 1nF; 0603
C36, C37: 47pF; 0603
C38: DNI; 0603
D5, D6: BAV19W; SOD123
J3: SJ
Q5: TIP29; TO220AV
Q6: TIP30; TO220AV
R18, R20, R22, R23, R26: 1.000k; 0603
R19: 1M; 0603
R21, R24: DNI; 0603
R25: 10.00k; 0603
R27: DNI; 2512
RO2: 1.00; LTO30
TP6: TESTPOINT
U9: BUF634; SO8
U10: ADA4898-2; SO8
U11: AD8276; SO8
U12: AD4898-1; SO8
X9: 1-227161-0; AMP_227161
X10: 22-23-2021
X11, X12: 22-23-2031

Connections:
GND: C25.2, C26.2, C27.1, C28.1, C29.2, C30.1, C31.2, C32.1, C34.1, C35.2, C39.2, C40.1, R26.2, X10.2; also elsewhere on the board
unnamed: C33.1, C34.2, R18.2, R19.1, U10.3 (IN+)
unnamed: C33.2, C35.1, R19.2, R20.2, U10.6 (IN-)
unnamed: R18.1, X9.2
unnamed: R20.1, X9.1
unnamed: C36.1, R21.2, R22.2, U10.2 (IN-)
unnamed: C37.1, R21.1, R23.2, U10.5 (IN+)
unnamed: C37.2, R23.1, U10.7 (OUT), U11.3 (+IN)
unnamed: C36.2, C38.1, R22.1, U10.1 (OUT), U11.2 (-IN)
unnamed: J3.1, Q5.B, Q6.B, U9.6 (OUT), X11.1, X12.1
unnamed: D5.A, D6.C, R27.2, RO2.P$2 (2), U12.3 (IN+), X10.1
unnamed: R24.1, U9.1 (BW)
unnamed: C38.2, U9.3 (IN), U11.6 (OUT)
unnamed: R25.2, TP6.P$1, U11.1 (REF), U12.6 (OUT)
unnamed: J3.2, Q5.E, Q6.E, R27.1, RO2.P$1 (1), U11.5 (SENSE), X11.3, X12.3
unnamed: R25.1, R26.1, U12.2 (IN-)
V+: C25.1, C26.1, C29.1, C31.1, C39.1, D5.C, Q5.C, U9.7 (V+), U10.8 (V+), U11.7 (V+), U12.7 (+VS), X12.2; also elsewhere on the board
V-: C27.2, C28.2, C30.2, C32.2, C40.2, D6.A, Q6.C, R24.2, U9.4 (V-), U10.4 (V-), U11.4 (V-), U12.4 (-VS), X11.2; also elsewhere on the board

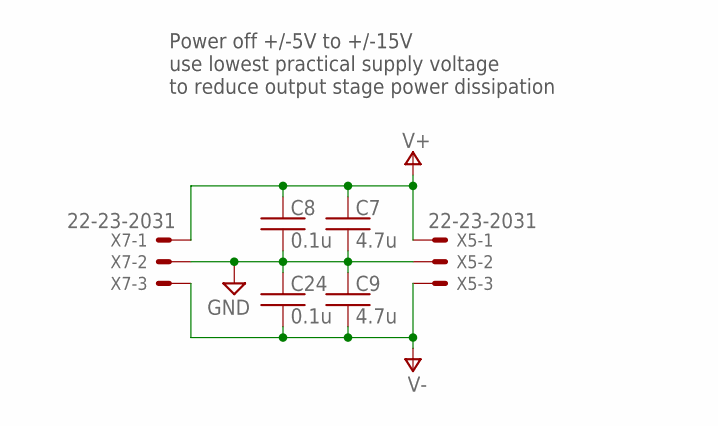
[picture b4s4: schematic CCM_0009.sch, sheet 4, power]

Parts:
C7, C9: 4.7u; 0603
C8, C24: 0.1u; 0603
X5, X7: 22-23-2031

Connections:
GND: C7.2, C8.2, C9.1, C24.1, X5.2, X7.2; also elsewhere on the board
V+: C7.1, C8.1, X5.1, X7.1; also elsewhere on the board
V-: C9.2, C24.2, X5.3, X7.3; also elsewhere on the board

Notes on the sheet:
Power off +/-5V to +/-15V use lowest practical supply voltage to reduce output stage power dissipation

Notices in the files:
parts and their libraries:
microbuilder: This work is placed in the public domain, and may be freely used for commercial and non-commercial work with the following conditions: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
